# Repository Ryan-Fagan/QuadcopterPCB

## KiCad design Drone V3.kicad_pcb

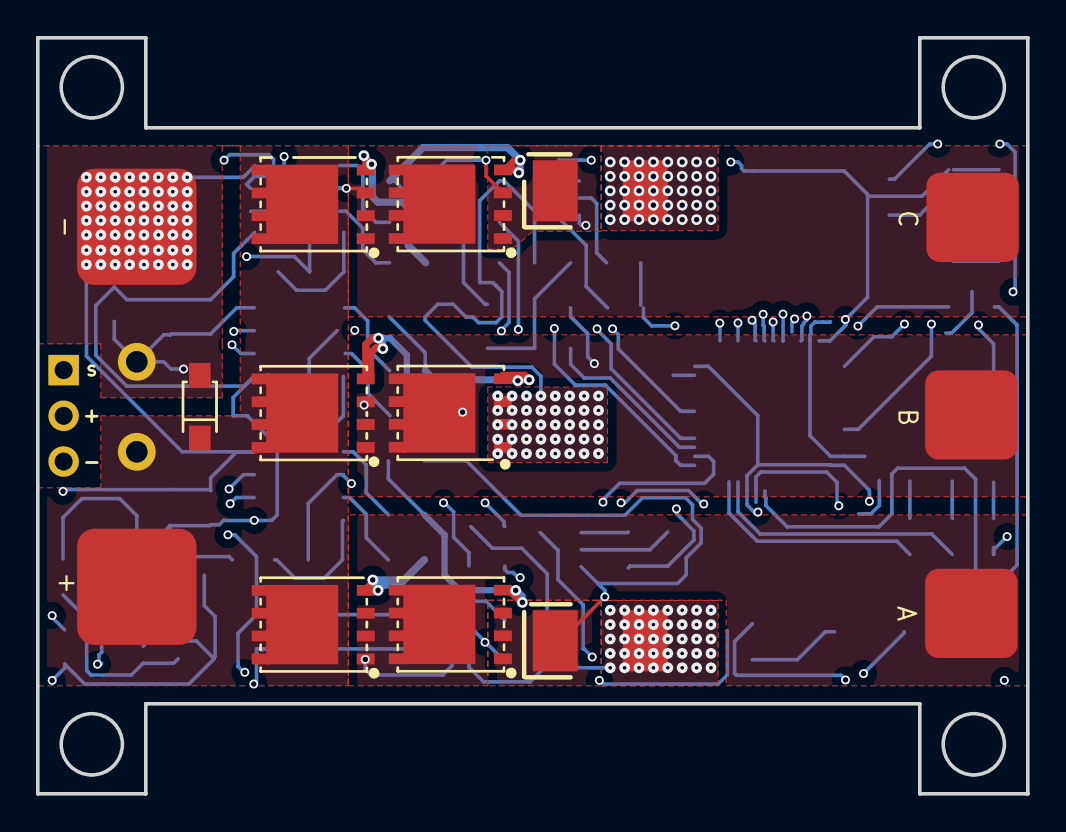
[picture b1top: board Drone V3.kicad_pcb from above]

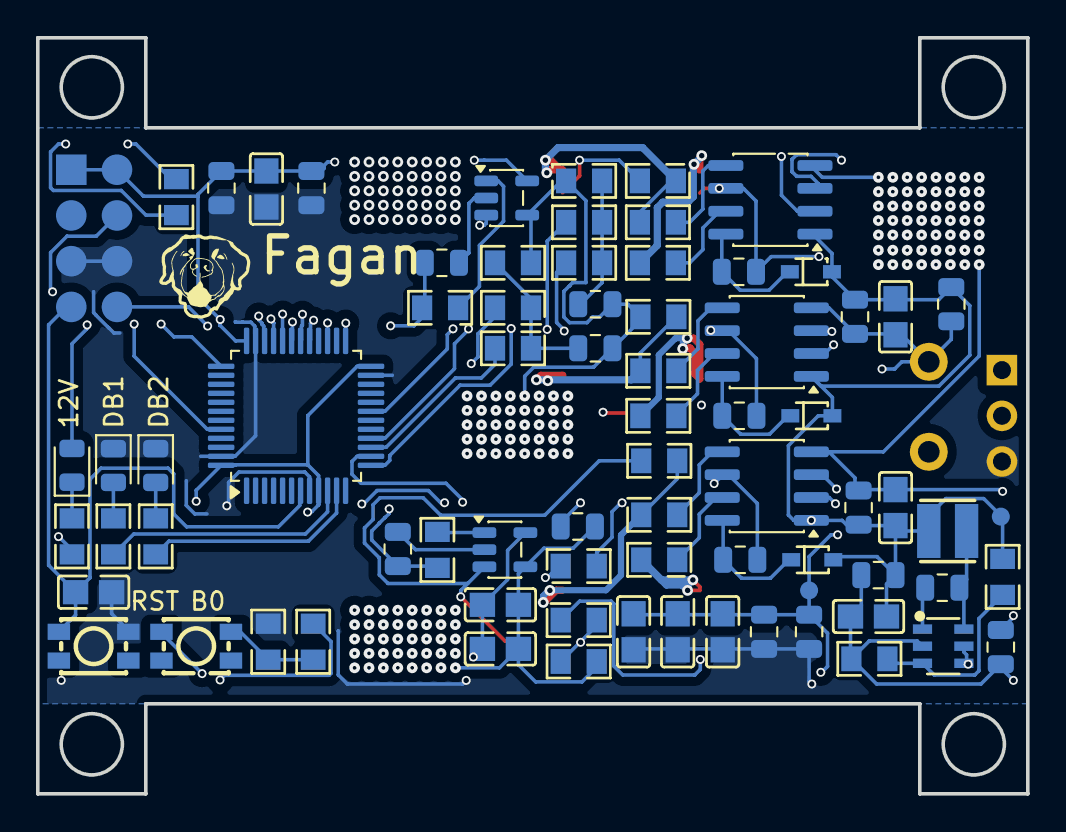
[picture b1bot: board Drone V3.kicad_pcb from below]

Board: 4 copper layers, 55.0 x 42.0 mm, 86 parts (75 on the bottom side), 59 nets.

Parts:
12V_SD1: TPS560430; SOT-23-6_L2.9-W1.6-P0.95-LS2.8-BL
B0: BOOT_Push; SW-SMD_4P-L3.5-W3.0-P1.50-LS4.7
C15, C20, C26, C28, C29, C33, C34, C35, C37, C39: 100n; C0805
C16, C21, C22, C23, C24, C32, C36, C41: 1u; C_0805_2012Metric
C19, C25, C27, C40, C49: 22n; C_0805_2012Metric
C30: 1000u; CAP-TH_BD12.5-P5.00-D0.6-FD
C31, C45: 10u; C_0805_2012Metric
C38: 10n; C_0805_2012Metric
C42: 2.2u; C_0805_2012Metric
C43: 100n; C_0805_2012Metric
D8, D10, D12: 1N5819WS; SOD-323_L1.8-W1.3-LS2.5-RD
D14, D15: LED; LED_0805_2012Metric
D17: BuckLED; LED_0805_2012Metric
J2: Phase Outputs; ESC Outputs
J3: Pad Terminals; Battery Inputs
J4: Signal; PinHeader_1x03_P2.54mm_Horizontal
L6: 33u; IND-SMD_L3.0-W3.0_LQH3NPN2R2NG0L
NMOS1, NMOS2, NMOS3, NMOS4, NMOS5, NMOS6: HYG025N06LS1C2; DFN-8_L5.9-W5.2-P1.27-LS6.2-BL
R9, R10, R16, R17, R23, R24: 10; R0805
R11, R18, R25, R31: 47k; R0805
R12, R21, R28: 36k; R0805
R13, R20, R27, R30, R35: 5k; R0805
R19, R26: 6E-4; RES-SMD_L6.4-W3.2_LRS2512
R22, R29, R32, R33, R34, R36, R37, R38: 220; R0805
R39: 243; R0805
R40: 22.1; R0805
RST: NRST_Push; SW-SMD_4P-L3.5-W3.0-P1.50-LS4.7
ST-Link1: ST-Conn; PinHeader_2x04_P2.54mm_Vertical
TVS1: SMF30A; SOD-123FL_L2.7-W1.8-LS3.8-RD
U1, U6, U7: IRS21867S; SOIC-8_3.9x4.9mm_P1.27mm
U4, U9: INA180A3; SOT-23-5
U13: STM32F303CBTx; LQFP-48_7x7mm_P0.5mm

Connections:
/ESC1/+3V3MCU: B0.1, C26.1, C29.1, C31.1, C32.1, C33.1, C34.1, C35.1, C36.1, C37.1, C38.1, J4.2, ST-Link1.1, ST-Link1.2, U4.5 (V+), U9.5 (V+), U13.9 (VDDA), U13.24 (VDD), U13.36 (VDD), U13.48 (VDD)
/ESC1/+12V: C15.1, C20.1, C21.1, C23.1, C24.1, C28.1, C45.1, D8.2 (A), D10.2 (A), D12.2 (A), D17.2 (A), L6.2, R39.1, U1.1 (VCC), U6.1 (VCC), U7.1 (VCC)
/ESC1/+ESC: C30.1, J3.1, NMOS1.1 (D), NMOS3.1 (D), NMOS5.1 (D), TVS1.1 (A1)
/ESC1/-3V3MCU: C31.2, C32.2, C33.2, C34.2, C35.2, C36.2, C37.2, C38.2, C39.1, D14.1 (K), D15.1 (K), J4.3, R31.1, RST.2, ST-Link1.5, ST-Link1.6, U13.8 (VSSA), U13.23 (VSS), U13.35 (VSS), U13.47 (VSS)
/ESC1/-ESC: 12V_SD1.2 (GND), C15.2, C19.1, C20.2, C21.2, C23.2, C24.2, C25.1, C26.2, C28.2, C29.2, C30.2, C42.2, C45.2, C49.1, J3.2, NMOS4.3 (S), R13.1, R18.2, R19.2, R20.1, R26.2, R27.1, R35.2, R40.2, TVS1.2 (A2), U1.4 (COM), U4.4 (-), U6.4 (COM), U7.4 (COM), U9.4 (-)
/ESC1/A_Phase: C16.2, J2.1, NMOS1.3 (S), NMOS2.1 (D), R12.2, U7.6 (VS)
/ESC1/BUCK_FB: 12V_SD1.3 (FB), R39.2, R40.1
/ESC1/BUCK_SW: 12V_SD1.6 (SW), C43.1, L6.1
/ESC1/B_Phase: C22.2, J2.2, NMOS3.3 (S), NMOS4.1 (D), R21.2, U1.6 (VS)
/ESC1/C_Phase: C41.2, J2.3, NMOS5.3 (S), NMOS6.1 (D), R28.2, U6.6 (VS)
/ESC1/MCU_AFB: R36.2, U13.14 (PA4)
/ESC1/MCU_AH: U7.2 (HIN), U13.29 (PA8)
/ESC1/MCU_AI: C40.1, R29.2, U13.25 (PB12)
/ESC1/MCU_AL: U7.3 (LIN), U13.32 (PA11)
/ESC1/MCU_BFB: R37.2, U13.15 (PA5)
/ESC1/MCU_BH: U1.2 (HIN), U13.30 (PA9)
/ESC1/MCU_BL: U1.3 (LIN), U13.33 (PA12)
/ESC1/MCU_CFB: R38.2, U13.16 (PA6)
/ESC1/MCU_CH: U6.2 (HIN), U13.31 (PA10)
/ESC1/MCU_CI: C27.1, R22.2, U13.27 (PB14)
/ESC1/MCU_CL: U6.3 (LIN), U13.19 (PB1)
/ESC1/NRST: C39.2, RST.1, ST-Link1.7, U13.7 (NRST)
/ESC1/SIG_ESC: J4.1, R34.2
/ESC1/SWCLK: ST-Link1.4, U13.37 (PA14)
/ESC1/SWDIO: ST-Link1.8, U13.34 (PA13)
/ESC1/Shunt_A: NMOS2.3 (S), R11.2, R26.1, U9.3 (+)
/ESC1/Shunt_C: NMOS6.3 (S), R19.1, R25.2, U4.3 (+)
unnamed: 12V_SD1.1 (CB), C43.2
unnamed: 12V_SD1.4 (EN), 12V_SD1.5 (VIN), C42.1
unnamed: B0.2, R30.1, R31.2
unnamed: C19.2, R12.1, R13.2, R36.1
unnamed: C25.2, R20.2, R21.1, R37.1
unnamed: C49.2, R27.2, R28.1, R38.1
unnamed: C16.1, D8.1 (K), U7.8 (VB)
unnamed: C22.1, D10.1 (K), U1.8 (VB)
unnamed: C41.1, D12.1 (K), U6.8 (VB)
unnamed: D14.2 (A), R32.2
unnamed: D15.2 (A), R33.2
unnamed: D17.1 (K), R35.1
unnamed: NMOS1.2 (G), R9.2
unnamed: NMOS2.2 (G), R10.2, R11.1
unnamed: NMOS3.2 (G), R16.2
unnamed: NMOS4.2 (G), R17.2, R18.1
unnamed: NMOS5.2 (G), R23.2
unnamed: NMOS6.2 (G), R24.2, R25.1
unnamed: R22.1, U4.1
unnamed: R29.1, U9.1
unnamed: R16.1, U1.7 (HO)
unnamed: R17.1, U1.5 (LO)
unnamed: C27.2, U4.2 (GND)
unnamed: R23.1, U6.7 (HO)
unnamed: R24.1, U6.5 (LO)
unnamed: R9.1, U7.7 (HO)
unnamed: R10.1, U7.5 (LO)
unnamed: C40.2, U9.2 (GND)
unnamed: R30.2, U13.44 (BOOT0)
unnamed: R32.1, U13.10 (PA0)
unnamed: R33.1, U13.11 (PA1)
unnamed: R34.1, U13.13 (PA3)

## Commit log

2025-11-05 Project Upload
2025-11-06 ESC Schematic Update
2025-11-12 ESC Update with Specifications
2025-11-12 ESC Final Draft 1
2025-11-17 ESC Update
2025-11-24 ESC Update & Finalization Draft
2025-12-31 Less bulky switching regulator for the ESC drivers, PCB update.
2026-01-18 Drone PCB Update
2026-01-31 ESC Routing, MOS Footprint Change
2026-02-01 Routing Update. Signal powers routed except for MCU. Look for unrouted traces without vias. Vias for signal lines added for organization
2026-04-01 Update Type stuff
2026-04-09 Done with routing, partial review complete.
2026-04-09 Final draft
2026-05-14 ESC PCB Finalized Iteration #1
2026-05-14 Custom Symbols & Footprints import
2026-05-14 Again
2026-05-14 Sensors & Main board start
2026-05-14 Library update with new symbols & footprints
2026-05-14 Initial component symbol placement
2026-05-15 Barometer & ToF Hierarchical Schematic Updates
2026-05-18 MCU implementation start Still needs component schematic checks & component integration with MCU
2026-05-21 Main Schematic update, Magnetometer deletions, Protocol connections, & External sensor compatibilities progress.
2026-05-21 GPS Schematic Update
2026-05-26 MCU Integration & Sensor Ports
2026-05-28 USB C integration, 5V tolerances on UART ports, digital pins, and analog pins.
2026-05-28 Docs Update
2026-05-29 Docs update
    Reorganization & added component diagram
2026-05-29 Component Diagram Replacement
2026-05-29 Component Diagram Bug Fix
